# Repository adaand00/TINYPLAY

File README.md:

# TINYPLAY
A tiny (46x25mm) game console using the attiny5

## Development
 The code is fully contained in main.c. The code was compiled and uploaded with microchip studio, using the standard settings for "attiny5 release". The gerber files were made in fusion360.

## BOM
* PCB
* ATTINY5-TS
* 8 bit Shift register - TI: SN74HCS164DR
* cr2032 battery holder - Linx: BAT-HLD-001-THM-TR 
* SMD slide switch - C&K: JS102011SAQN 
* 15x 0805 red LEDs
* 2x 6x6mm tactile buttons
* sod123 diode
* various 0603 resistors and capacitors
 
 ## Future development
  - [ ] Make it smaller (!Important!)
  - [ ] Improve programming headers
  - [ ] Make the game more fun
  - [ ] Add more pixels

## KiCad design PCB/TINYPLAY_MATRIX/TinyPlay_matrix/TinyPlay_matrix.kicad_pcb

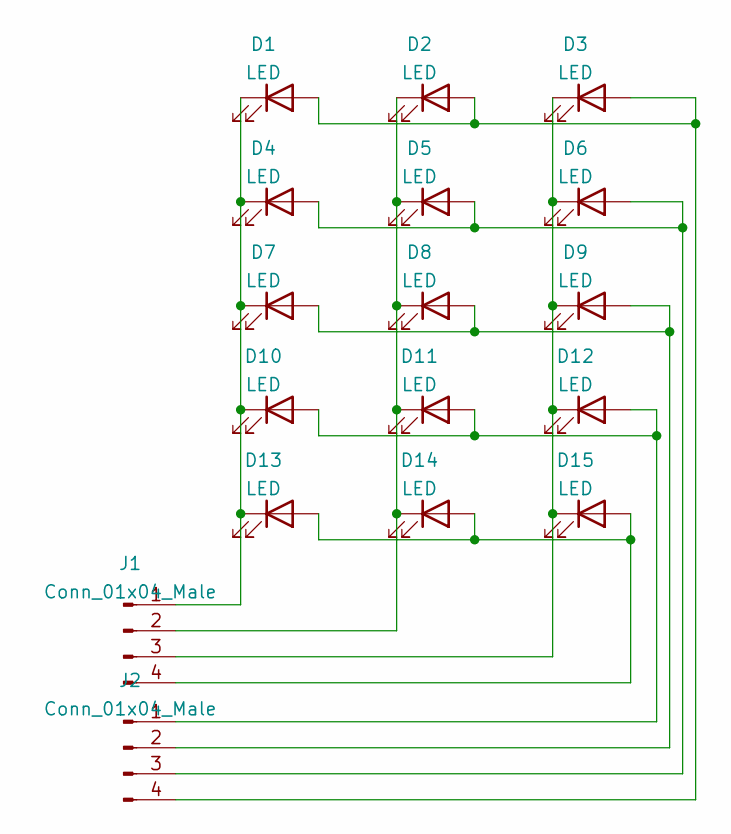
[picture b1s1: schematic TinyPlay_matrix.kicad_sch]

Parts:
D1, D2, D3, D4, D5, D6, D7, D8, D9, D10, D11, D12, D13, D14, D15: LED; LED_0603_1608Metric_Pad1.05x0.95mm_HandSolder
J1, J2: Conn_01x04_Male; PinHeader_1x04_P1.27mm_Vertical

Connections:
unnamed: D1.1 (K), D4.1 (K), D7.1 (K), D10.1 (K), D13.1 (K), J1.1
unnamed: D1.2 (A), D2.2 (A), D3.2 (A), J2.4
unnamed: D4.2 (A), D5.2 (A), D6.2 (A), J2.3
unnamed: D7.2 (A), D8.2 (A), D9.2 (A), J2.2
unnamed: D10.2 (A), D11.2 (A), D12.2 (A), J2.1
unnamed: D2.1 (K), D5.1 (K), D8.1 (K), D11.1 (K), D14.1 (K), J1.2
unnamed: D3.1 (K), D6.1 (K), D9.1 (K), D12.1 (K), D15.1 (K), J1.3
unnamed: D13.2 (A), D14.2 (A), D15.2 (A), J1.4

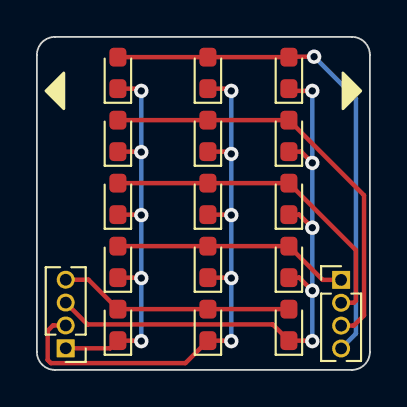
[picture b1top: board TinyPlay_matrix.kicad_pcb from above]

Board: 2 copper layers, 18.5 x 18.5 mm, 17 parts (0 on the bottom side), 8 nets.

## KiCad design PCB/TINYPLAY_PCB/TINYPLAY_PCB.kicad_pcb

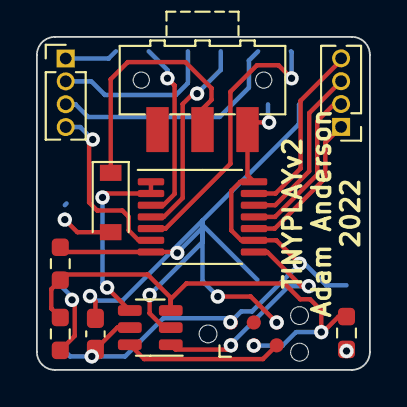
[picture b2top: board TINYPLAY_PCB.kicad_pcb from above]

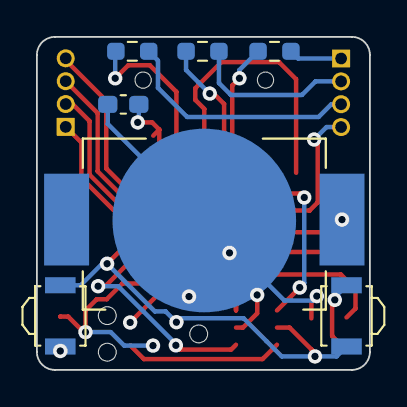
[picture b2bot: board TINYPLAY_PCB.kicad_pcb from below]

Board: 2 copper layers, 18.5 x 18.5 mm, 18 parts (7 on the bottom side), 21 nets.

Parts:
BT1: Battery_Cell; BAT_BAT-HLD-012-SMT
C1, C2: 100nF; C_0603_1608Metric_Pad1.08x0.95mm_HandSolder
D1: 1N4148W; D_SOD-123
J1: Conn_02x03_Odd_Even; Tag-Connect_TC2030-IDC-NL_2x03_P1.27mm_Vertical
J6, J7: Conn_01x04_Male; PinHeader_1x04_P1.27mm_Vertical
R1: 6.8k; R_0603_1608Metric_Pad0.98x0.95mm_HandSolder
R2: 15k; R_0603_1608Metric_Pad0.98x0.95mm_HandSolder
R3: 10k; R_0603_1608Metric_Pad0.98x0.95mm_HandSolder
R4, R5, R6: 1k; R_0603_1608Metric_Pad0.98x0.95mm_HandSolder
SW1: SW_SPDT; SW_SPDT_CK-JS102011SAQN
SW2, SW3: SW_Push; SW_SPST_B3U-3000P
U1: ATtiny5-TS; SOT-23-6
U2: 74HC164; TSSOP-14_4.4x5mm_P0.65mm

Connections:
/PB0: J1.1, U1.1 (PB0), U2.8 (CP)
/PB1: J1.3, R1.1, R2.1, R3.1, U1.3 (PB1)
/PB2: U1.4 (PB2), U2.1 (DSA), U2.2 (DSB)
/PB3: J1.5, U1.6 (~RESET/PB3)
GND: BT1.N, C1.2, C2.2, J1.6, R3.2, U1.2 (GND), U2.7 (GND)
unnamed: BT1.P2, D1.2 (A)
unnamed: D1.1 (K), SW1.2 (B)
unnamed: J6.1, R4.2
unnamed: J6.2, R5.2
unnamed: J6.3, R6.2
unnamed: J6.4, U2.6 (Q3)
unnamed: J7.1, U2.10 (Q4)
unnamed: J7.2, U2.11 (Q5)
unnamed: J7.3, U2.12 (Q6)
unnamed: J7.4, U2.13 (Q7)
unnamed: R1.2, SW2.1
unnamed: R2.2, SW3.1
unnamed: R4.1, U2.3 (Q0)
unnamed: R5.1, U2.4 (Q1)
unnamed: R6.1, U2.5 (Q2)
VDD: C1.1, C2.1, J1.2, SW1.1 (A), SW2.2, SW3.2, U1.5 (VCC), U2.9 (~MR), U2.14 (VCC)

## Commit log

2021-11-02 Add gerber files
2022-01-28 Start new version using kicad
2022-03-01 Version 2.0
2022-04-03 Code for v2
2022-12-01 config changes
